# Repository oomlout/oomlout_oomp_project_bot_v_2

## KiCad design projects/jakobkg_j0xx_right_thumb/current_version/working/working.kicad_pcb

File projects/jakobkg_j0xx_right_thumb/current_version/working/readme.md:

# j0xx
 
## summary 
* id: jakobkg_j0xx_right_thumb
* user: jakobkg
* name: j0xx
* board: right_thumb
* repo: https://github.com/jakobkg/j0xx
* src_file_repo_kicad_pcb: pcb/right_thumb/right_thumb.kicad_pcb
* src_file_repo_kicad_pcb_link: https://github.com/jakobkg/j0xx/tree/main/pcb/right_thumb/right_thumb.kicad_pcb
* src_file_repo_kicad_sch: pcb/right_thumb/right_thumb.kicad_sch
* src_file_repo_kicad_sch_link: https://github.com/jakobkg/j0xx/tree/main/pcb/right_thumb/right_thumb.kicad_sch

* src_file_repo_sch: 
* src_file_repo_sch_link: https://github.com/jakobkg/j0xx/tree/main/
* full details link: https://github.com/oomlout/oomlout_oomp_project_bot_v_2/tree/main/projects/jakobkg_j0xx_right_thumb/current_version/working

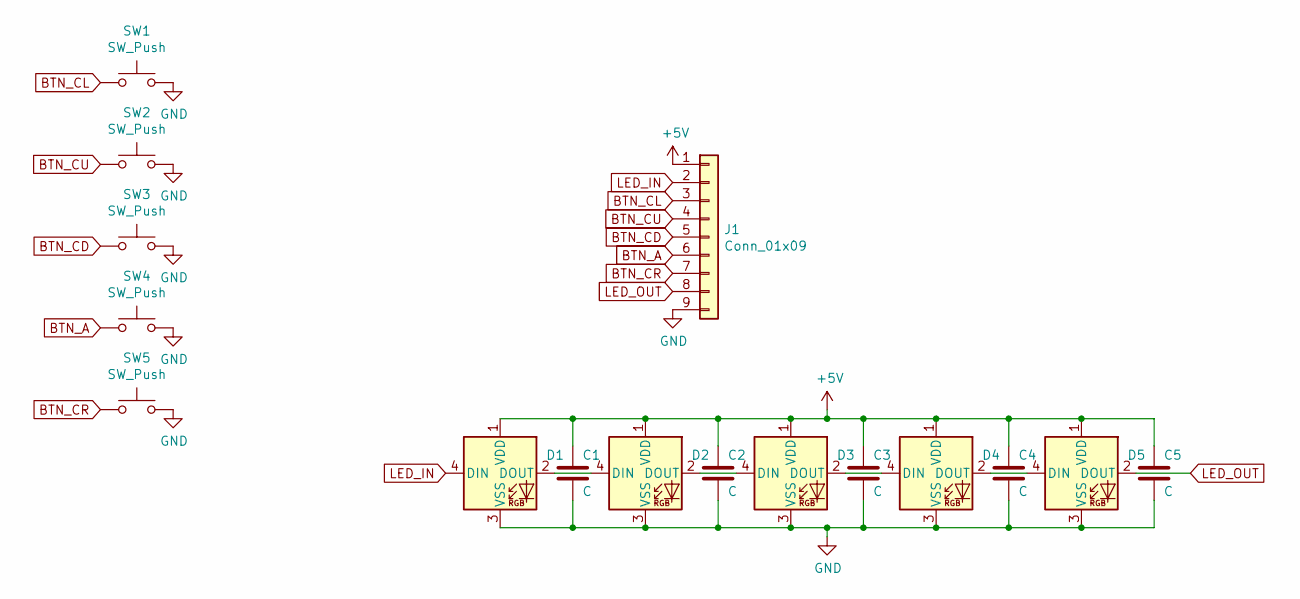
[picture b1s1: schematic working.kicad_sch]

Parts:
C1, C2, C3, C4, C5: C; C_0805_2012Metric
D1, D2, D3, D4, D5: WS2812B; LED_WS2812B_PLCC4_5.0x5.0mm_P3.2mm
J1: Conn_01x09; PinHeader_1x09_P2.54mm_Vertical
SW1, SW2, SW3, SW4, SW5: SW_Push; MX+Choc_socket

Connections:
+5V: C1.1, C2.1, C3.1, C4.1, C5.1, D1.1 (VDD), D2.1 (VDD), D3.1 (VDD), D4.1 (VDD), D5.1 (VDD), J1.1
BTN_A: J1.6, SW4.1
BTN_CD: J1.5, SW3.1
BTN_CL: J1.3, SW1.1
BTN_CR: J1.7, SW5.1
BTN_CU: J1.4, SW2.1
GND: C1.2, C2.2, C3.2, C4.2, C5.2, D1.3 (VSS), D2.3 (VSS), D3.3 (VSS), D4.3 (VSS), D5.3 (VSS), J1.9, SW1.2, SW2.2, SW3.2, SW4.2, SW5.2
LED_IN: D1.4 (DIN), J1.2
LED_OUT: D5.2 (DOUT), J1.8
unnamed: D1.2 (DOUT), D2.4 (DIN)
unnamed: D2.2 (DOUT), D3.4 (DIN)
unnamed: D3.2 (DOUT), D4.4 (DIN)
unnamed: D4.2 (DOUT), D5.4 (DIN)

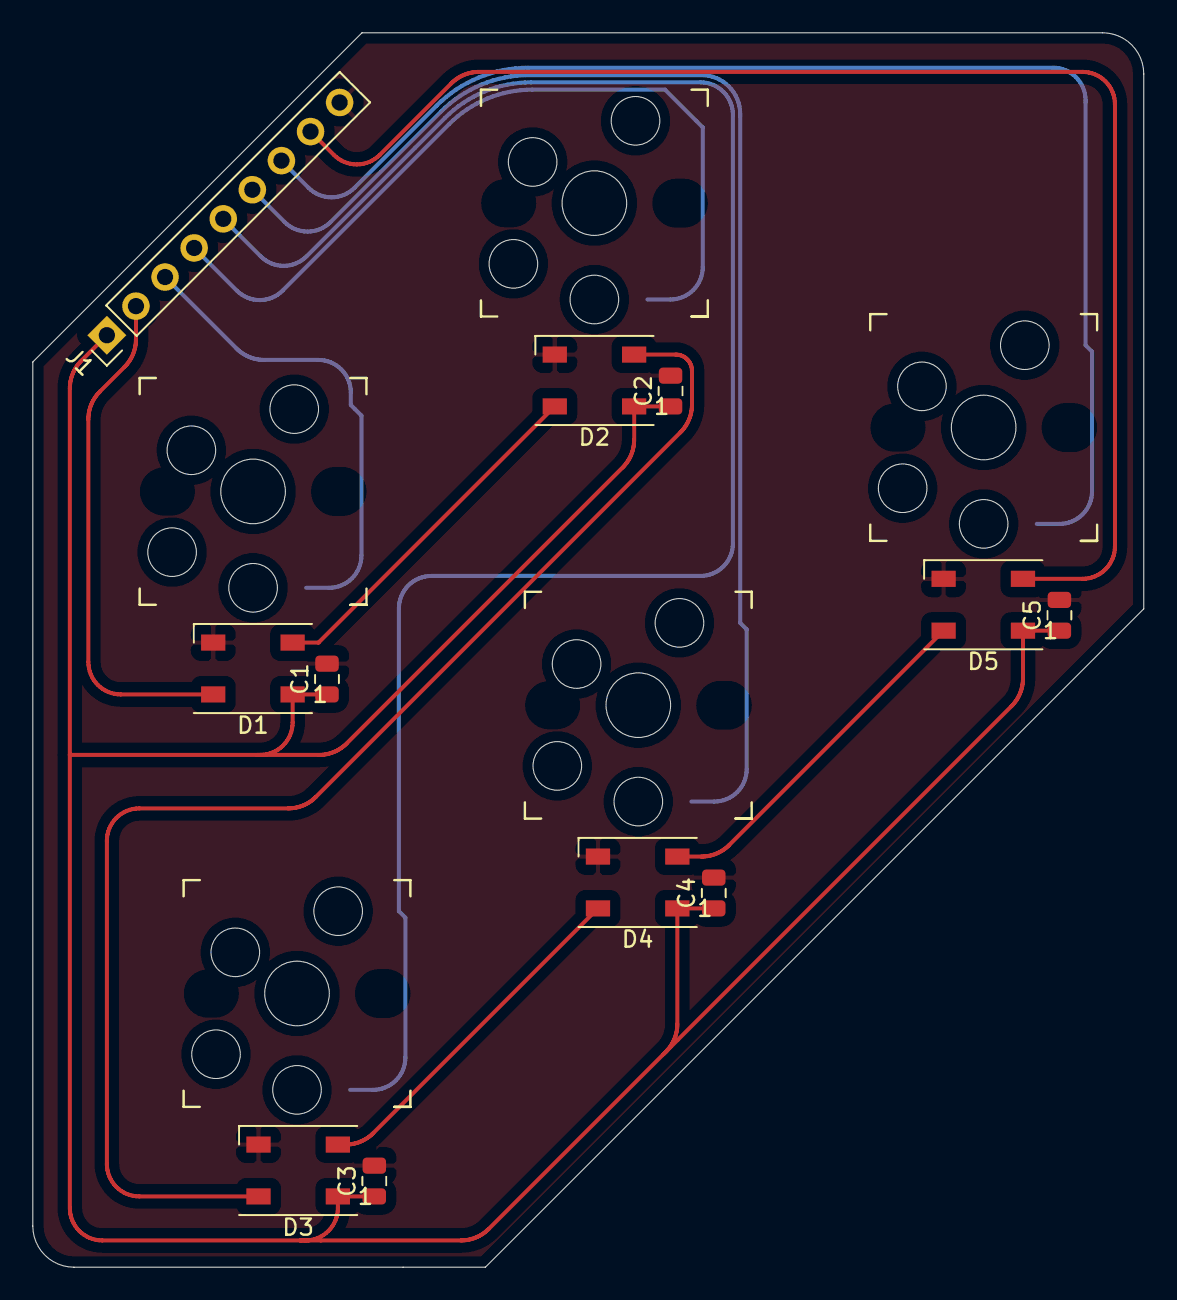
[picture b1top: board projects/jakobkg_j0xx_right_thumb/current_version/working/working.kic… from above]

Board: 2 copper layers, 68.6 x 76.2 mm, 16 parts (0 on the bottom side), 13 nets.

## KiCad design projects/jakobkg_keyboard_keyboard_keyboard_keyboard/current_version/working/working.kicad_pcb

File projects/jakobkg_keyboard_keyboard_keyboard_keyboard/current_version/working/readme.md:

# keyboard_keyboard
 
## summary 
* id: jakobkg_keyboard_keyboard_keyboard_keyboard
* user: jakobkg
* name: keyboard_keyboard
* board: keyboard_keyboard
* repo: https://github.com/jakobkg/keyboard_keyboard
* src_file_repo_kicad_pcb: keyboard_keyboard.kicad_pcb
* src_file_repo_kicad_pcb_link: https://github.com/jakobkg/keyboard_keyboard/tree/master/keyboard_keyboard.kicad_pcb

* src_file_repo_sch: keyboard_keyboard.sch
* src_file_repo_sch_link: https://github.com/jakobkg/keyboard_keyboard/tree/master/keyboard_keyboard.sch
* full details link: https://github.com/oomlout/oomlout_oomp_project_bot_v_2/tree/main/projects/jakobkg_keyboard_keyboard_keyboard_keyboard/current_version/working

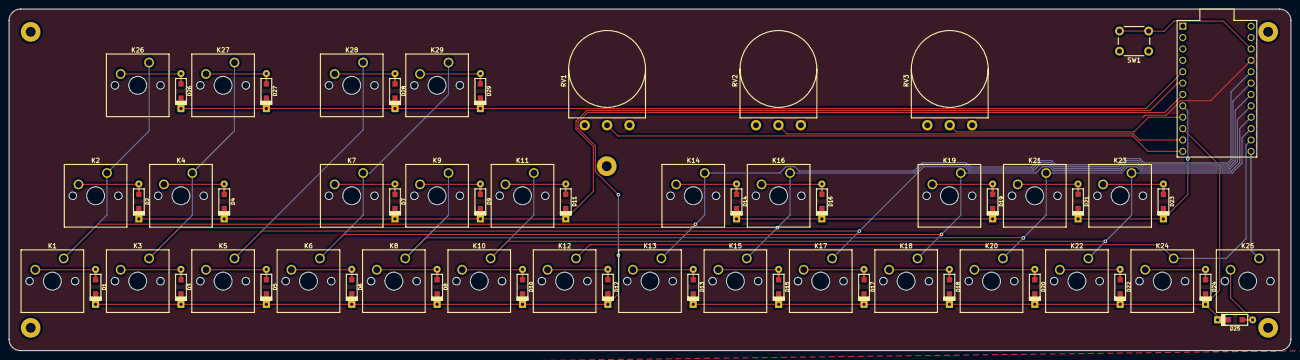
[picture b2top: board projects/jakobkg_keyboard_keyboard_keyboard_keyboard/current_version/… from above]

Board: 2 copper layers, 286.0 x 76.2 mm, 68 parts (0 on the bottom side), 48 nets.

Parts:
D1, D2, D3, D4, D5, D6, D7, D8, D9, D10, D11, D12, D13, D14, D15, D16, D17, D18, D19, D20, D21, D22, D23, D24, D25, D26, D27, D28, D29: D; D_SOD123_axial
H1, H2, H3, H4, H5: MountingHole; MountingHole_2.2mm_M2_Pad
K1, K2, K3, K4, K5, K6, K7, K8, K9, K10, K11, K12, K13, K14, K15, K16, K17, K18, K19, K20, K21, K22, K23, K24, K25, K26, K27, K28, K29: KEYSW; SW_Cherry_MX_1.00u_PCB
RV1, RV2, RV3: R_POT; Potentiometer_Omeg_PC16BU_Vertical
SW1: SW_PUSH; SW_PUSH_6mm
U1: ProMicro

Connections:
Col1: K1.1, K2.1, K13.1, K14.1, K26.1, U1.20
Col2: K3.1, K4.1, K15.1, K16.1, K27.1, U1.19
Col3: K5.1, K17.1, K28.1, U1.18
Col4: K6.1, K7.1, K18.1, K19.1, K29.1, U1.17
Col5: K8.1, K9.1, K20.1, K21.1, U1.16
Col6: K10.1, K11.1, K22.1, K23.1, U1.15
Col7: K12.1, K24.1, U1.14
Col8: K25.1, U1.13
GND: RV1.3, RV2.3, RV3.3, SW1.1, U1.3, U1.4, U1.23
ModRow: D26.1, D27.1, D28.1, D29.1, U1.5
unnamed: D1.2, K1.2
unnamed: D2.2, K2.2
unnamed: D3.2, K3.2
unnamed: D4.2, K4.2
unnamed: D5.2, K5.2
unnamed: D6.2, K6.2
unnamed: D7.2, K7.2
unnamed: D8.2, K8.2
unnamed: D9.2, K9.2
unnamed: D10.2, K10.2
unnamed: D11.2, K11.2
unnamed: D12.2, K12.2
unnamed: D13.2, K13.2
unnamed: D14.2, K14.2
unnamed: D15.2, K15.2
unnamed: D16.2, K16.2
unnamed: D17.2, K17.2
unnamed: D18.2, K18.2
unnamed: D19.2, K19.2
unnamed: D20.2, K20.2
unnamed: D21.2, K21.2
unnamed: D22.2, K22.2
unnamed: D23.2, K23.2
unnamed: D24.2, K24.2
unnamed: D25.2, K25.2
unnamed: D26.2, K26.2
unnamed: D27.2, K27.2
unnamed: D28.2, K28.2
unnamed: D29.2, K29.2
Pot1: RV1.2, U1.12
Pot2: RV2.2, U1.11
Pot3: RV3.2, U1.9
RESET: SW1.2, U1.22
Row1: D2.1, D4.1, D7.1, D9.1, D11.1, U1.6
Row2: D1.1, D3.1, D5.1, D6.1, D8.1, D10.1, D12.1, U1.7
Row3: D14.1, D16.1, D19.1, D21.1, D23.1, U1.8
Row4: D13.1, D15.1, D17.1, D18.1, D20.1, D22.1, D24.1, D25.1, U1.10
VCC: RV1.1, RV2.1, RV3.1, U1.21

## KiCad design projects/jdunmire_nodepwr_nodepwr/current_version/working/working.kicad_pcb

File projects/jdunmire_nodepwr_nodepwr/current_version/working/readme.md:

# nodepwr
 
## summary 
* id: jdunmire_nodepwr_nodepwr
* user: jdunmire
* name: nodepwr
* board: nodepwr
* repo: https://github.com/jdunmire/nodePWR
* src_file_repo_kicad_pcb: nodePWR.kicad_pcb
* src_file_repo_kicad_pcb_link: https://github.com/jdunmire/nodePWR/tree/master/nodePWR.kicad_pcb

* src_file_repo_sch: nodePWR.sch
* src_file_repo_sch_link: https://github.com/jdunmire/nodePWR/tree/master/nodePWR.sch
* full details link: https://github.com/oomlout/oomlout_oomp_project_bot_v_2/tree/main/projects/jdunmire_nodepwr_nodepwr/current_version/working

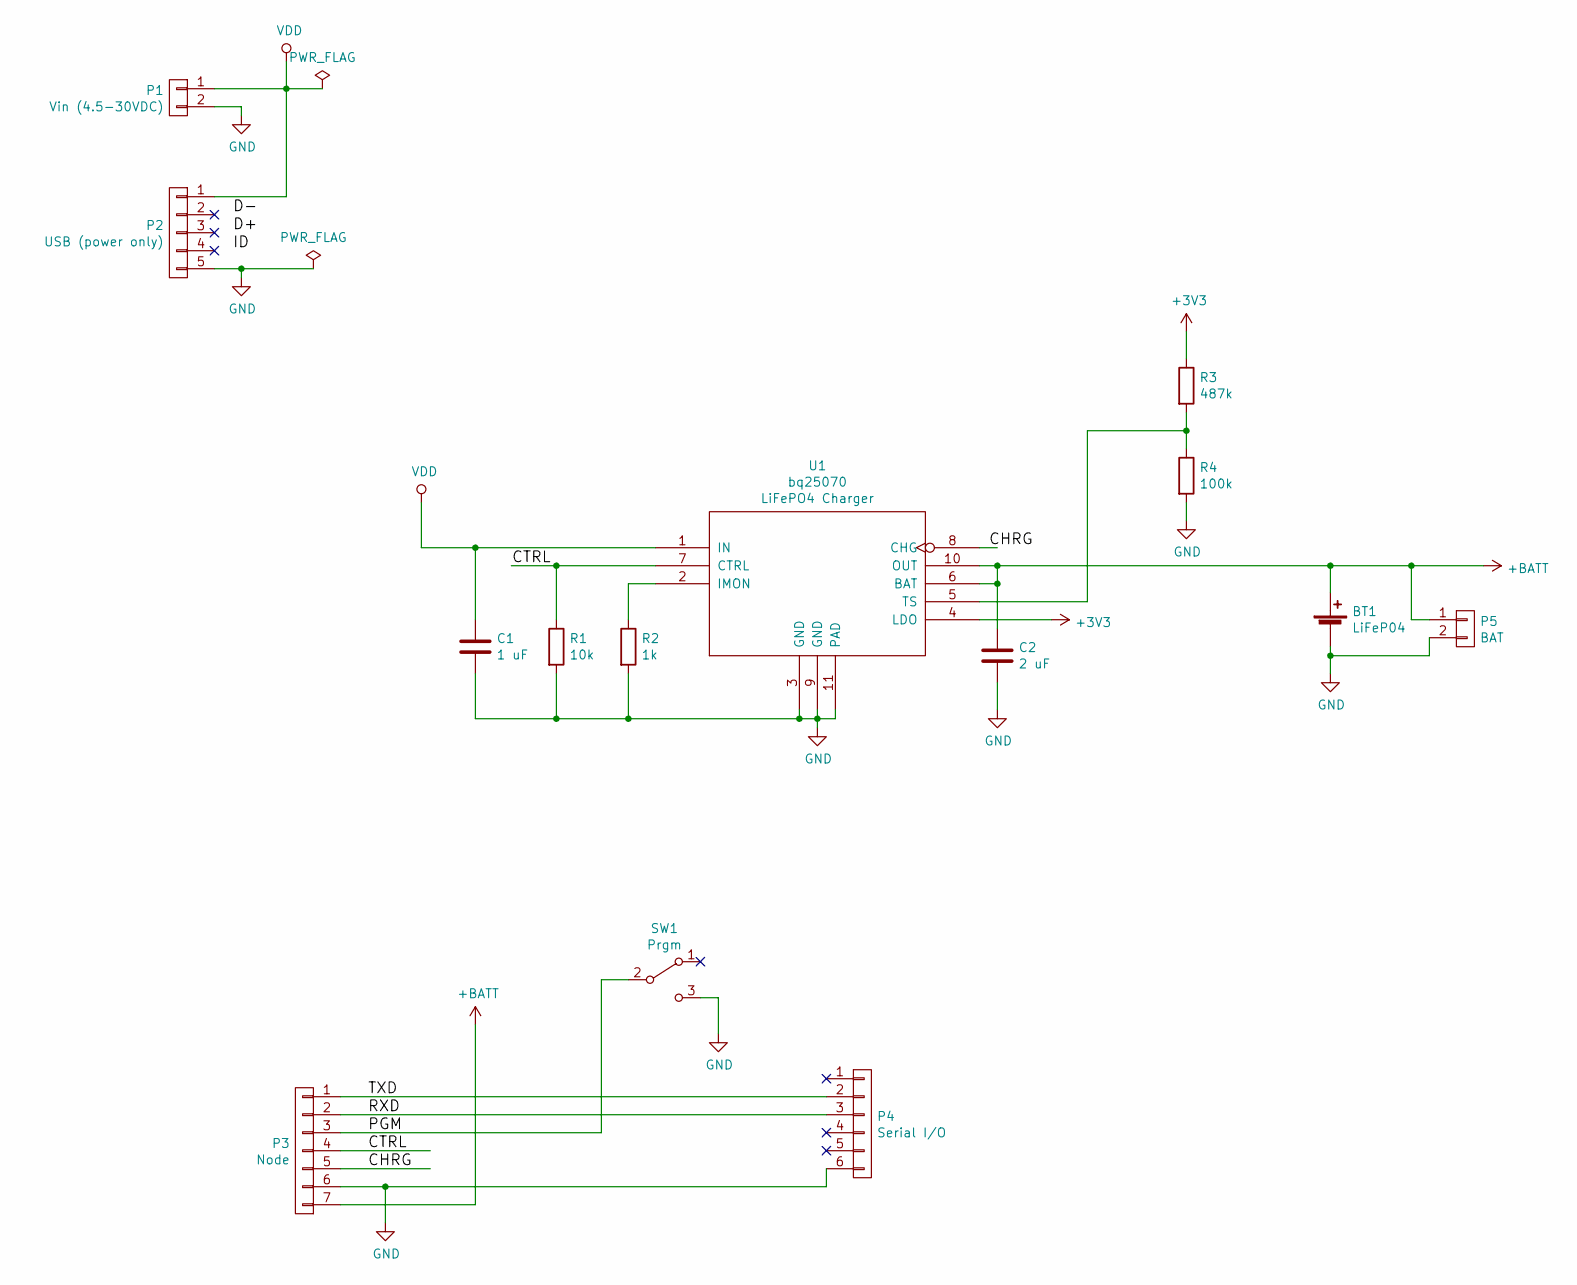
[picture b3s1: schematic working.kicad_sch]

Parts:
BT1: LiFeP04; JST_PH_S2B-PH-SM4-TB_02x2.00mm_Angled
C1: 1 uF; C_0603
C2: 2 uF; C_0603
P1: Vin (4.5-30VDC); Pin_Header_Straight_1x02
P2: USB (power only); USB_Micro-B_10103594-0001LF
P3: Node; FPC_conn-7_8x4.9mm_Pitch0.5mm
P4: Serial I/O; Pin_Header_Straight_1x06
P5: BAT; Pin_Header_Straight_1x02
R1: 10k; R_0603
R2: 1k; R_0603
R3: 487k; R_0603
R4: 100k; R_0603
SW1: Prgm; SW_SPDT_PCM12
U1: bq25070; bq25070_DQC_10-DQC10_P84X2P4

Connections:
+3V3: R3.1, U1.4 (LDO)
+BATT: BT1.1 (+), C2.1, P3.7, P5.1, U1.6 (BAT), U1.10 (OUT)
/CHRG: P3.5, U1.8 (CHG)
/CTRL: P3.4, R1.1, U1.7 (CTRL)
/PGM: P3.3, SW1.2 (B)
/RXD: P3.2, P4.3
/TXD: P3.1, P4.2
GND: BT1.2 (-), C1.2, C2.2, P1.2, P2.5, P3.6, P4.6, P5.2, R1.2, R2.2, R4.2, SW1.3 (C), U1.3 (GND), U1.9 (GND), U1.11 (PAD)
unnamed: R2.1, U1.2 (IMON)
unnamed: R3.2, R4.1, U1.5 (TS)
VDD: C1.1, P1.1, P2.1, U1.1 (IN)

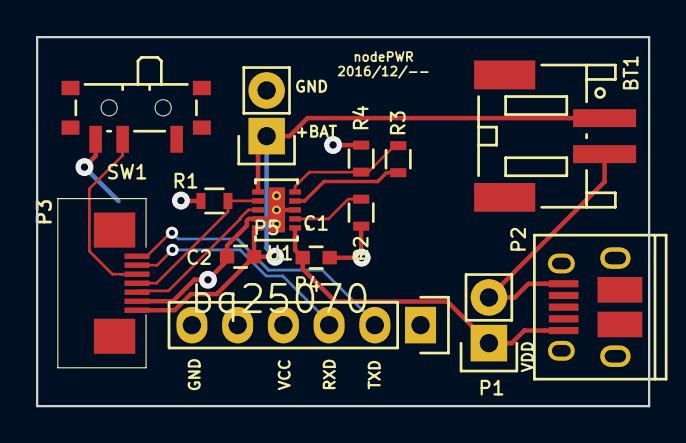
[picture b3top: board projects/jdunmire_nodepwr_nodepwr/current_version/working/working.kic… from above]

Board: 2 copper layers, 34.0 x 20.5 mm, 14 parts (0 on the bottom side), 11 nets.

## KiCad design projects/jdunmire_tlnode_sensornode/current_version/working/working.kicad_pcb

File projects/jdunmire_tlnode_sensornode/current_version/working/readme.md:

# tlnode
 
## summary 
* id: jdunmire_tlnode_sensornode
* user: jdunmire
* name: tlnode
* board: sensornode
* repo: https://github.com/jdunmire/TLnode
* src_file_repo_kicad_pcb: sensorNode.kicad_pcb
* src_file_repo_kicad_pcb_link: https://github.com/jdunmire/TLnode/tree/master/sensorNode.kicad_pcb

* src_file_repo_sch: sensorNode.sch
* src_file_repo_sch_link: https://github.com/jdunmire/TLnode/tree/master/sensorNode.sch
* full details link: https://github.com/oomlout/oomlout_oomp_project_bot_v_2/tree/main/projects/jdunmire_tlnode_sensornode/current_version/working

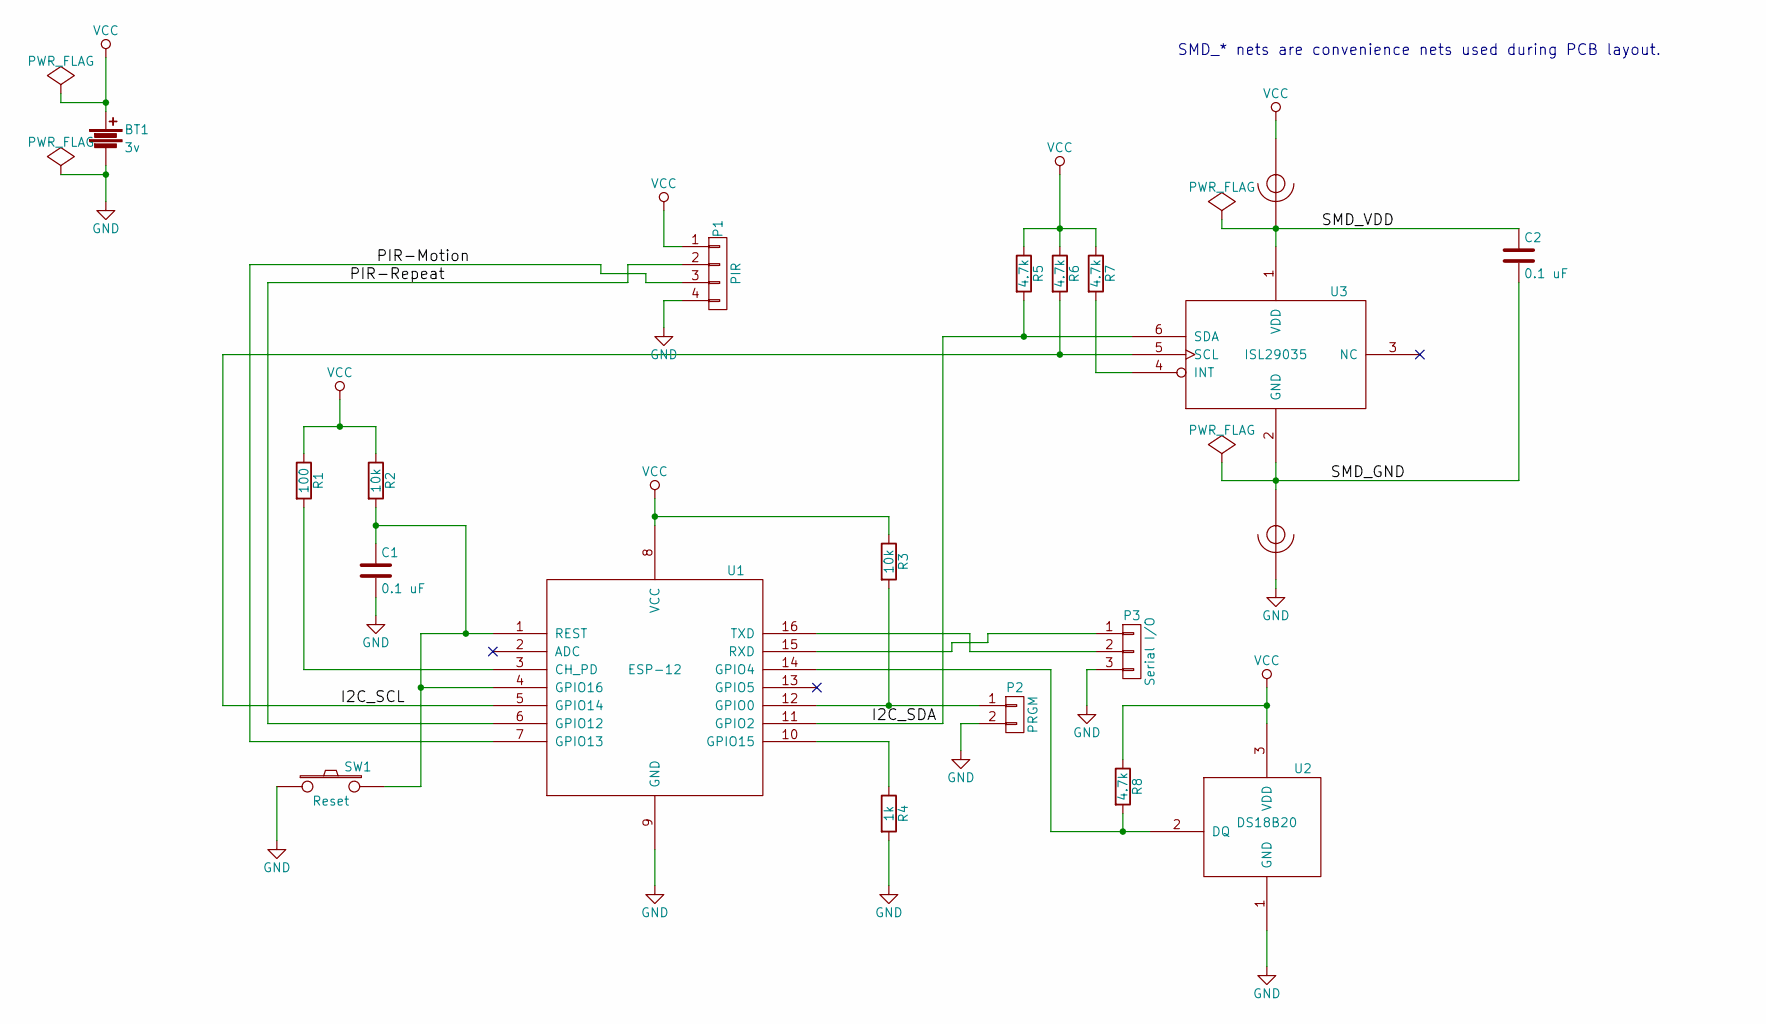
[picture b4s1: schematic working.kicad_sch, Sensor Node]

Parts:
BT1: 3v; BA2AAPC
C1, C2: 0.1 uF; C_0603_HandSoldering
NT1, NT2: Net-Tie-2; NetTie-I_Connected_SMD
P1: PIR; Pin_Header_Angled_1x04
P2: PRGM; Pin_Header_Angled_1x02
P3: Serial I/O; Pin_Header_Angled_1x03
R1: 100; R_0603_HandSoldering
R2, R3: 10k; R_0603_HandSoldering
R4: 1k; R_0603_HandSoldering
R5, R6, R7, R8: 4.7k; R_0603_HandSoldering
SW1: Reset; SW_SPST_E-Switch_TL3302BF180QG
U1: ESP-12
U2: DS18B20; TO-92_Inline_Narrow_Oval
U3: ISL29035; DFN-6_1.5x1.6mm_Pitch0.5mm

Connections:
/I2C_SCL: R6.2, U1.5 (GPIO14), U3.5 (SCL)
/I2C_SDA: R5.2, U1.11 (GPIO2), U3.6 (SDA)
/PIR-Motion: P1.3, U1.7 (GPIO13)
/PIR-Repeat: P1.2, U1.6 (GPIO12)
/SMD_GND: C2.2, NT2.1, U3.2 (GND)
/SMD_VDD: C2.1, NT1.2, U3.1 (VDD)
GND: BT1.2, C1.2, NT2.2, P1.4, P2.2, P3.3, R4.2, SW1.1, U1.9 (GND), U2.1 (GND)
unnamed: C1.1, R2.2, SW1.2, U1.1 (REST), U1.4 (GPIO16)
unnamed: P2.1, R3.2, U1.12 (GPIO0)
unnamed: P3.1, U1.15 (RXD)
unnamed: P3.2, U1.16 (TXD)
unnamed: R1.2, U1.3 (CH_PD)
unnamed: R4.1, U1.10 (GPIO15)
unnamed: R7.2, U3.4 (INT)
unnamed: R8.2, U1.14 (GPIO4), U2.2 (DQ)
VCC: BT1.1, NT1.1, P1.1, R1.1, R2.1, R3.1, R5.1, R6.1, R7.1, R8.1, U1.8 (VCC), U2.3 (VDD)

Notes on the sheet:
SMD_* nets are convenience nets used during PCB layout.

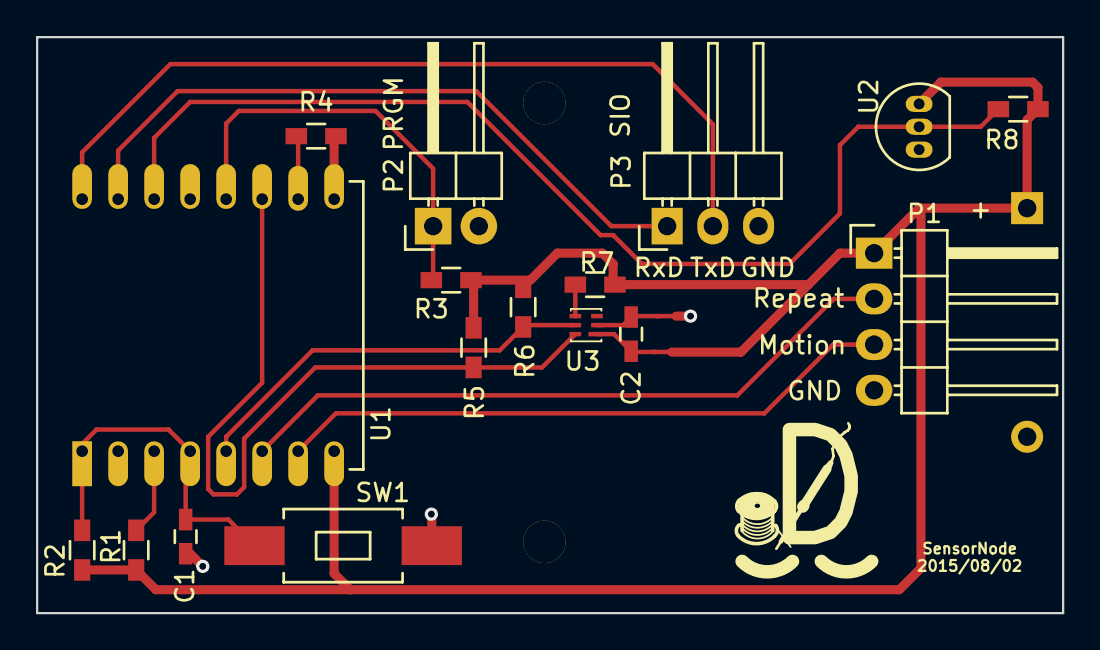
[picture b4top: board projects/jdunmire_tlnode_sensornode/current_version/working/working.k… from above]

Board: 2 copper layers, 57.0 x 32.0 mm, 20 parts (1 on the bottom side), 16 nets.

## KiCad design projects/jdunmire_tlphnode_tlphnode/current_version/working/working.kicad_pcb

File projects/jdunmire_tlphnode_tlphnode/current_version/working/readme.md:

# tlphnode
 
## summary 
* id: jdunmire_tlphnode_tlphnode
* user: jdunmire
* name: tlphnode
* board: tlphnode
* repo: https://github.com/jdunmire/TLPHnode
* src_file_repo_kicad_pcb: TLPHnode.kicad_pcb
* src_file_repo_kicad_pcb_link: https://github.com/jdunmire/TLPHnode/tree/master/TLPHnode.kicad_pcb

* src_file_repo_sch: TLPHnode.sch
* src_file_repo_sch_link: https://github.com/jdunmire/TLPHnode/tree/master/TLPHnode.sch
* full details link: https://github.com/oomlout/oomlout_oomp_project_bot_v_2/tree/main/projects/jdunmire_tlphnode_tlphnode/current_version/working

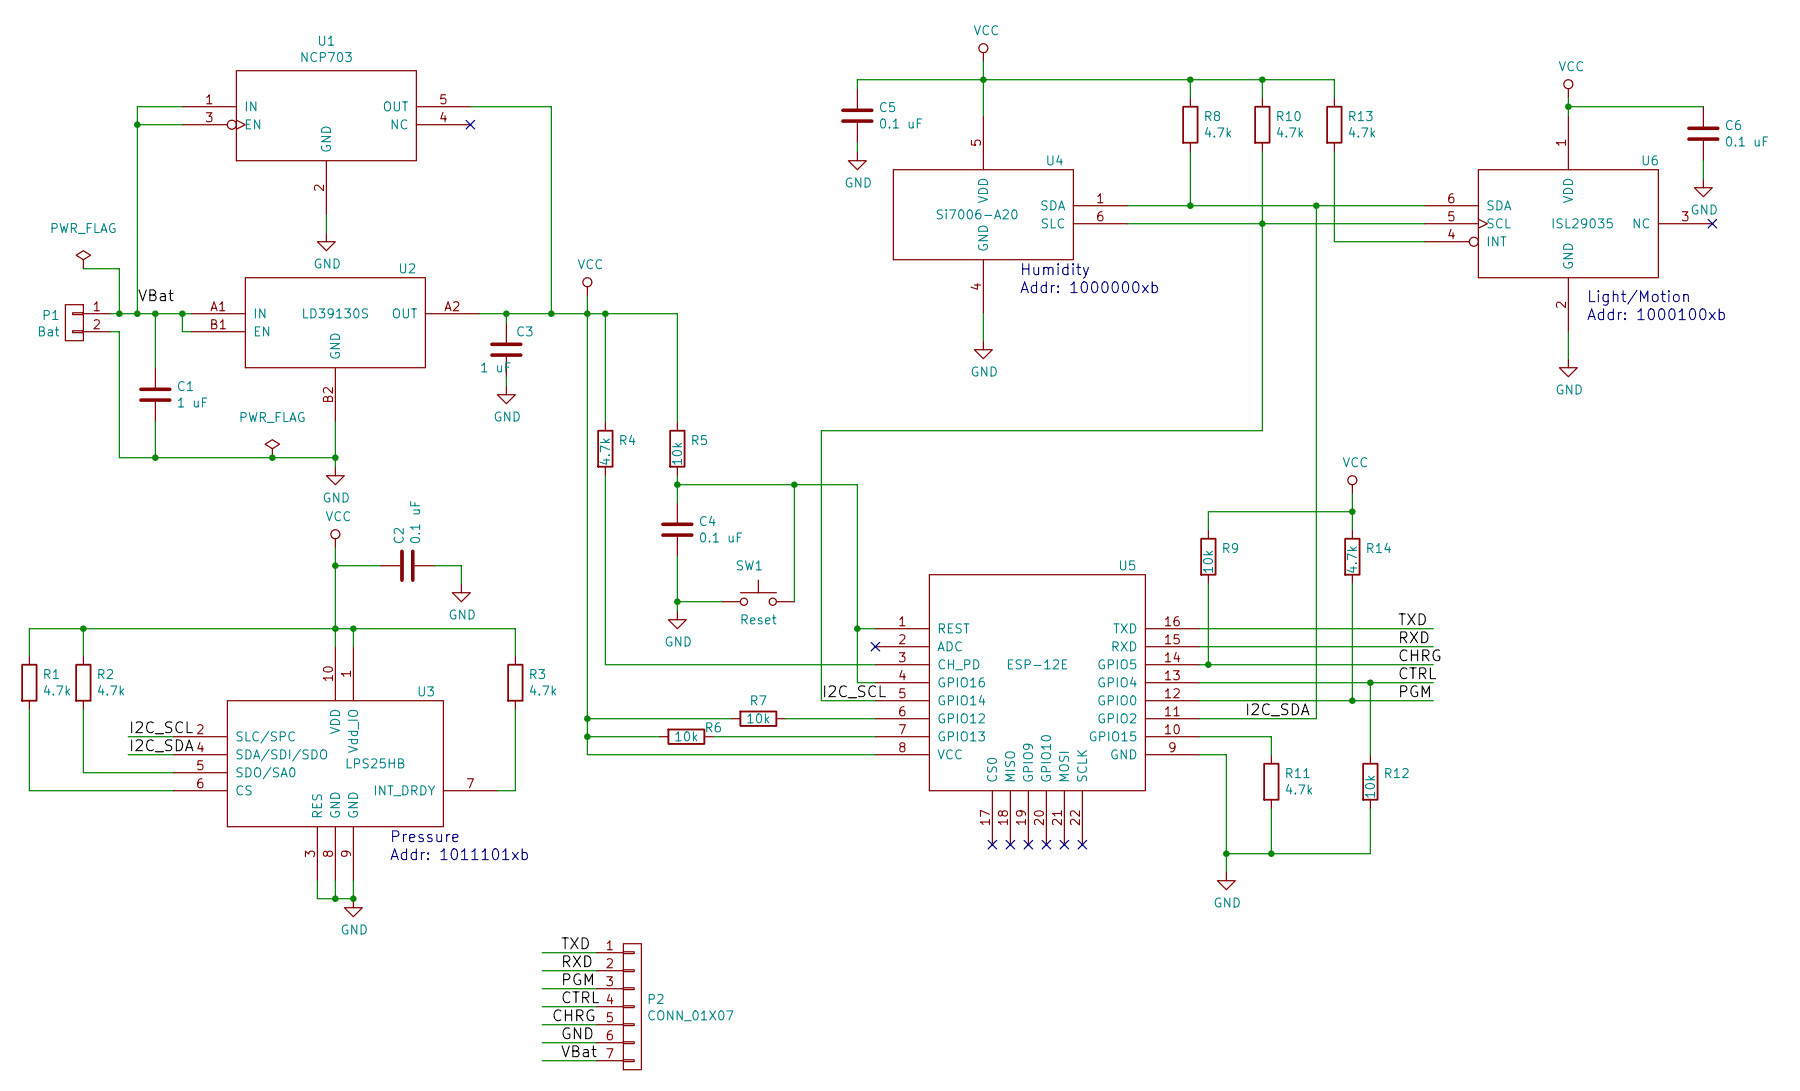
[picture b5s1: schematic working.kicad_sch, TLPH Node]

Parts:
C1, C3: 1 uF; C_0603
C2, C4, C5, C6: 0.1 uF; C_0603
P1: Bat; Pin_Header_Straight_1x02
P2: CONN_01X07; FPC_conn-7_8x4.9mm_Pitch0.5mm
R1, R2, R3, R4, R8, R10, R11, R13, R14: 4.7k; R_0603
R5, R6, R7, R9, R12: 10k; R_0603
SW1: Reset; ESwitch-SMD-4
U1: NCP703; NCP703-TSOP-5
U2: LD39130S; LD39130S-FlipChip-4
U3: LPS25HB; LPS25HB-HLGA-10L-2.5x2.5mm
U4: Si7006-A20; Si7006_A20-DFN-6
U5: ESP-12E
U6: ISL29035; ISL29035-DFN-6-1.5x1.6mm_Pitch0.5mm

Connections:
/CHRG: P2.5, R9.2, U5.14 (GPIO5)
/CTRL: P2.4, R12.1, U5.13 (GPIO4)
/I2C_SCL: R10.2, U3.2 (SLC/SPC), U4.6 (SLC), U5.5 (GPIO14), U6.5 (SCL)
/I2C_SDA: R8.2, U3.4 (SDA/SDI/SDO), U4.1 (SDA), U5.11 (GPIO2), U6.6 (SDA)
/PGM: P2.3, R14.2, U5.12 (GPIO0)
/RXD: P2.2, U5.15 (RXD)
/TXD: P2.1, U5.16 (TXD)
/VBat: C1.1, P1.1, P2.7, U1.1 (IN), U1.3 (EN), U2.A1 (IN), U2.B1 (EN)
GND: C1.2, C2.2, C3.2, C4.2, C5.2, C6.2, P1.2, P2.6, R11.2, R12.2, SW1.1, U1.2 (GND), U2.B2 (GND), U3.3 (RES), U3.8 (GND), U3.9 (GND), U4.4 (GND), U5.9 (GND), U6.2 (GND)
unnamed: C4.1, R5.2, SW1.2, U5.1 (REST), U5.4 (GPIO16)
unnamed: R1.2, U3.6 (CS)
unnamed: R2.2, U3.5 (SDO/SA0)
unnamed: R3.2, U3.7 (INT_DRDY)
unnamed: R4.2, U5.3 (CH_PD)
unnamed: R6.1, U5.7 (GPIO13)
unnamed: R7.1, U5.6 (GPIO12)
unnamed: R11.1, U5.10 (GPIO15)
unnamed: R13.2, U6.4 (INT)
VCC: C2.1, C3.1, C5.1, C6.1, R1.1, R2.1, R3.1, R4.1, R5.1, R6.2, R7.2, R8.1, R9.1, R10.1, R13.1, R14.1, U1.5 (OUT), U2.A2 (OUT), U3.1 (Vdd_IO), U3.10 (VDD), U4.5 (VDD), U5.8 (VCC), U6.1 (VDD)

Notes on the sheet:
Humidity
Pressure
Addr: 1000000xb
Light/Motion
Addr: 1000100xb
Addr: 1011101xb

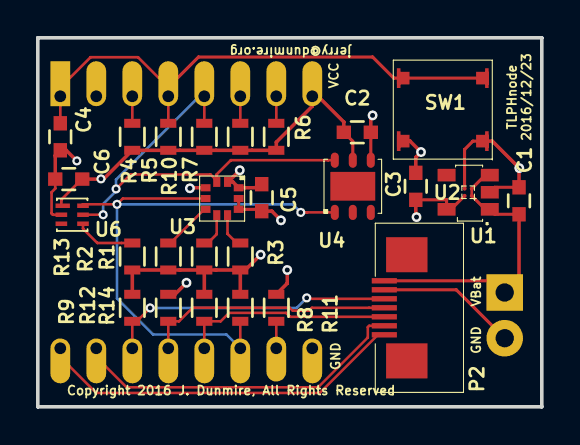
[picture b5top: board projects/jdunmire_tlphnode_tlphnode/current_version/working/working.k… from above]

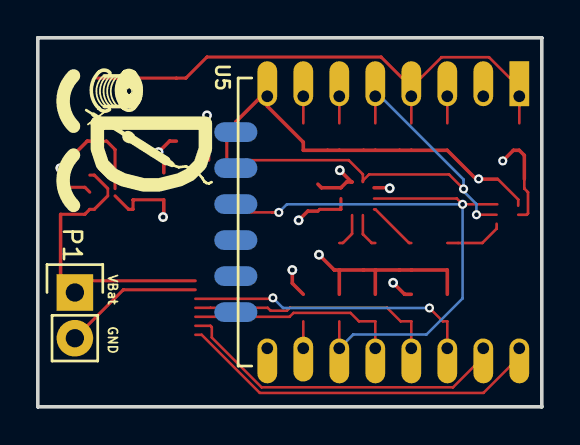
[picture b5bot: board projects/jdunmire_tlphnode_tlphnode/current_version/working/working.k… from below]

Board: 4 copper layers, 28.0 x 20.5 mm, 30 parts (3 on the bottom side), 19 nets.

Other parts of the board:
Ref**: RockingDLogo_9x7

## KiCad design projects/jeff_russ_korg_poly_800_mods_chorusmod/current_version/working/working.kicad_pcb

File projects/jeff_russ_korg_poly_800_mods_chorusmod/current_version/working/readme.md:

# korg_poly_800_mods
 
## summary 
* id: jeff_russ_korg_poly_800_mods_chorusmod
* user: jeff_russ
* name: korg_poly_800_mods
* board: chorusmod
* repo: https://github.com/Jeff-Russ/Korg_Poly-800_Mods
* src_file_repo_kicad_pcb: ChorusMod.kicad_pcb
* src_file_repo_kicad_pcb_link: https://github.com/Jeff-Russ/Korg_Poly-800_Mods/tree/master/ChorusMod.kicad_pcb

* src_file_repo_sch: ChorusMod.sch
* src_file_repo_sch_link: https://github.com/Jeff-Russ/Korg_Poly-800_Mods/tree/master/ChorusMod.sch
* full details link: https://github.com/oomlout/oomlout_oomp_project_bot_v_2/tree/main/projects/jeff_russ_korg_poly_800_mods_chorusmod/current_version/working

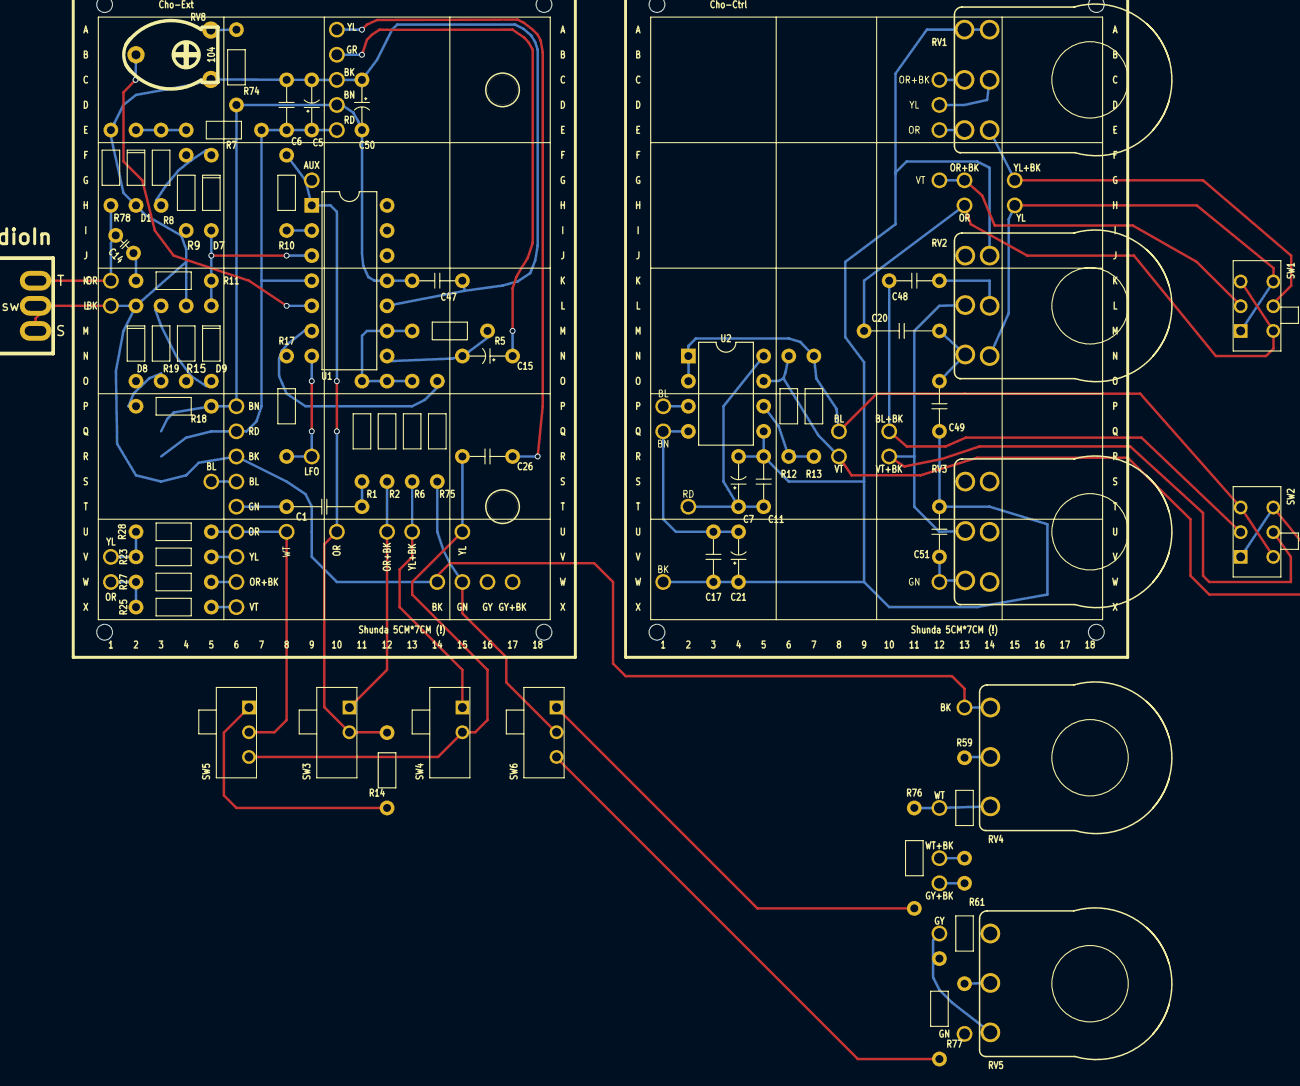
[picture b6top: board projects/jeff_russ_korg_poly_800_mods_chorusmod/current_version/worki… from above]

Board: 2 copper layers, 118 parts (0 on the bottom side), 80 nets.

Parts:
C1: 0.1µ; 300Mil_TH_C
C5, C50: 1µ; 200Mil_TH_CP
C6, C11, C17, C47, C48, C49, C51: 0.1µ; 200Mil_TH_C
C7, C21: 1µ; 200Mil_TH_CP_no3D
C14: 2.2µ; 100Mil_TH_C
C15: 10µ; 200Mil_TH_CP
C20: 1µ; 300Mil_TH_C_no3D
C26: 2.2µ; 200Mil_TH_C
D1, D8: 2v2; 300Mil_TH_Diode
D7, D9: 1N4148; 300Mil_TH_Diode
Drill1, Drill2: 3mm_DrillHole
J1: AuxAudioIn; TS_Jack_Switched_Generic
J1.11: WT; Conn_Female_Dupont-1_Val
J1.12, J2.3: BK; Conn_Female_Dupont-1_Val
J1.13, J2.6: OR; Conn_Female_Dupont-1_Val
J1.14: YL; Conn_Female_Dupont-1
J1.15, J2.8: OR+BK; Conn_Female_Dupont-1_Val
J1.16: YL+BK; Conn_Female_Dupont-1_Val
J1.17, J2.5: GN; Conn_Female_Dupont-1_Val
J2.1: BN; Conn_Female_Dupont-1_Val
J2.2: RD; Conn_Female_Dupont-1_Val
J2.4: BL; Conn_Female_Dupont-1_Val
J2.7: YL; Conn_Female_Dupont-1_Val
J2.9: VT; Conn_Female_Dupont-1_Val
JAUX.1: BK; Conn_Female_Dupont-1_Val
JAUX.2: OR; Conn_Female_Dupont-1_Val
JAUX.3: AUX; Conn_Female_Dupont-1_Val
JLFO.1: LFO; Conn_Female_Dupont-1_Val
PCB1: Shunda 5CM*7CM (!); perfboard_24x18_Shunda_misprint
R1, R6: 22K; 400Mil_TH_Resistor
R2: 33K; 400Mil_TH_Resistor
R5: 22K; 300Mil_TH_Resistor
R7, R18: 1K; 300Mil_TH_Resistor
R8, R9, R15, R19: 470; 300Mil_TH_Resistor
R10, R11: 5.1K; 300Mil_TH_Resistor
R12, R13: 47K; 400Mil_TH_Resistor
R14: 15K; 300Mil_TH_Resistor
R17, R77: 1.5M; 400Mil_TH_Resistor
R23, R25: 18K; 300Mil_TH_Resistor
R27, R28: 33K; 300Mil_TH_Resistor
R59: 10K; 400Mil_TH_Resistor
R61: 4.7K; 400Mil_TH_Resistor
R74: 1M; 300Mil_TH_Resistor
R75: 1M; 400Mil_TH_Resistor
R76: 220K; 400Mil_TH_Resistor
R78: 470K; 300Mil_TH_Resistor
RV1: DUAL_B250K; 400x100Mil_TH_Pot_Dual_FaceUp_FlipGangs
RV2: DUAL_B100K; 400x100Mil_TH_Pot_Dual_FaceUp
RV3: B10K; 400x500Mil_TH_Pot_reinfoced_FaceUp
RV4: B100K; 400Mil_TH_Pot_FaceUp
RV5: B1M; 400Mil_TH_Pot_FaceUp
RV8: 104; trimmer_extended_wiper
SW1: ChoFilterPan; TH_DPDT_Angled
SW2: ChoFbInv; TH_DPDT_Angled
SW3: AuxToChorus; TH_SPST_Angled
SW4: KorgToChorus; TH_SPST_Angled
SW5: DrySource; TH_SPDT_Angled
SW6: LFO2 Sel; TH_SPDT_Angled
U1: TL084; 300Mil_DIP14
U2: NJM4556; 300Mil_DIP8
W1, W2.7, W8: YL; TH_Wire_Val
W1.1: GY+BK; Conn_Female_Dupont-1
W1.2: GY; Conn_Female_Dupont-1
W1.5: BK; Conn_Female_Dupont-1_Val
W1.6: GN; Conn_Female_Dupont-1_Val
W1.7: GY; Conn_Female_Dupont-1_Val
W1.8: GY+BK; Conn_Female_Dupont-1_Val
W1.9: WT; Conn_Female_Dupont-1_Val
W1.10: WT+BK; Conn_Female_Dupont-1_Val
W2: GR; TH_Wire_Val
W2.1, W4: BN; TH_Wire_Val
W2.2, W5: RD; TH_Wire_Val
W2.3, W3: BK; TH_Wire_Val
W2.4, W6: BL; TH_Wire_Val
W2.5: GN; TH_Wire_Val
W2.6, W7: OR; TH_Wire_Val
W2.8: OR+BK; TH_Wire_Val
W2.9: VT; TH_Wire_Val
W.Inv.I1: VT; TH_Wire
W.Inv.I2: BL; TH_Wire
W.Inv.O1: BL+BK; TH_Wire
W.Inv.O2: VT+BK; TH_Wire
W.Pan.I1: YL; TH_Wire
W.Pan.I2: OR; TH_Wire
W.Pan.O1: OR+BK; TH_Wire
W.Pan.O2: YL+BK; TH_Wire

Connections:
/HPWet: RV2.6, W.Pan.I1.1
/LPWet: C20.2, W.Pan.I2.1
/PreHP: C48.1, W.Inv.O1.1
/PreLP: RV2.2, RV3.2, W.Inv.O2.1
/Squ: W1.2.2, W1.7.2
/WetInv: R12.1, U2.7, W.Inv.I1.1
unnamed: C1.1, J2.5.1
unnamed: C1.2, R1.2
unnamed: C5.1, C6.2, J2.2.1, R7.2, U1.4, W5.1
unnamed: C7.1, C11.1, U2.8, W2.2.1
unnamed: C7.2, C11.2, C17.2, C21.1, C49.2, C51.2, RV1.1, RV1.4, RV2.4, U2.5, W2.3.1
unnamed: C14.1, R11.1
unnamed: C14.2, JAUX.2.1, R78.1
unnamed: C15.1, W2.1
unnamed: C15.2, R5.2, U1.8
unnamed: C17.1, C21.2, U2.4, W2.1.1
unnamed: C20.1, C49.1, RV2.3
unnamed: C26.1, J1.14.1
unnamed: C26.2, W1.1
unnamed: C47.1, C50.2, J2.1.1, R18.2, R74.2, U1.11, W4.1
unnamed: C5.2, C6.1, C47.2, C50.1, D1.2, D8.1, J1.12.1, J2.3.1, JAUX.1.1, R9.1, R15.2, R78.2, RV8.1, U1.10, W3.1
unnamed: C48.2, RV2.5
unnamed: C51.1, RV3.3, W2.5.1
unnamed: D1.1, R7.1, R8.1
unnamed: D7.1, R8.2, R9.2
unnamed: D7.2, D9.1, R11.2, U1.3
unnamed: D8.2, R18.1, R19.1
unnamed: D9.2, R15.1, R19.2
unnamed: J1.1, JAUX.2.2
unnamed: J1.2, J1.3, JAUX.1.2
unnamed: J1.11.1, J2.6.1, R28.2
unnamed: J1.11.2, SW5.2
unnamed: J1.12.2, W1.5.2
unnamed: J1.13.1, JAUX.3.1, R10.2, U1.1
unnamed: J1.13.2, R14.2, SW3.2
unnamed: J1.14.2, SW4.2, SW5.3
unnamed: J1.15.1, R2.2
unnamed: J1.15.2, SW3.1
unnamed: J1.16.1, R6.2
unnamed: J1.16.2, SW4.1
unnamed: J1.17.1, R75.1
unnamed: J1.17.2, SW6.2
unnamed: J2.4.1, W6.1
unnamed: J2.7.1, R23.2
unnamed: J2.8.1, R27.2
unnamed: J2.9.1, R25.2
unnamed: JLFO.1.1, R17.1, U1.7
unnamed: R1.1, R2.1, R5.1, R6.1, U1.9
unnamed: R10.1, U1.2
unnamed: R12.2, R13.2, U2.6
unnamed: R13.1, U2.1, U2.2, W.Inv.I2.1
unnamed: R14.1, SW5.1
unnamed: R17.2, R75.2, U1.6
unnamed: R23.1, R28.1, W8.1
unnamed: R25.1, R27.1, W7.1
unnamed: R59.1, RV4.2
unnamed: R59.2, W1.10.1
unnamed: R61.1, RV5.2
unnamed: R61.2, W1.1.1, W1.8.1
unnamed: R74.1, RV8.3
unnamed: R76.1, RV4.3, W1.9.1
unnamed: R76.2, SW6.1
unnamed: R77.1, SW6.3
unnamed: R77.2, RV5.3, W1.2.1, W1.7.1
unnamed: RV1.2, W2.7.1
unnamed: RV1.3, W.Pan.O2.1
unnamed: RV1.5, W2.8.1
unnamed: RV1.6, W2.6.1
unnamed: RV4.1, W1.5.1
unnamed: RV8.2, U1.5
unnamed: SW1.1, SW1.6, W.Pan.I1.2
unnamed: SW1.2, W.Pan.O1.2
unnamed: SW1.3, SW1.4, W.Pan.I2.2
unnamed: SW1.5, W.Pan.O2.2
unnamed: SW2.1, SW2.6, W.Inv.I1.2
unnamed: SW2.2, W.Inv.O1.2
unnamed: SW2.3, SW2.4, W.Inv.I2.2
unnamed: SW2.5, W.Inv.O2.2
unnamed: U2.3, W2.4.1
unnamed: W2.9.1, W.Pan.O1.1

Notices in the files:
projects/jdunmire_nodepwr_nodepwr/current_version/working/working.kicad_pcb:
Copyright 2016, J. Dunmire
All Rights reserved.
projects/jdunmire_tlnode_sensornode/current_version/working/working.kicad_pcb:
Copyright 2015 J. Dunmire
projects/jdunmire_tlphnode_tlphnode/current_version/working/working.kicad_pcb:
Copyright 2016 J. Dunmire, All Rights Reserved
